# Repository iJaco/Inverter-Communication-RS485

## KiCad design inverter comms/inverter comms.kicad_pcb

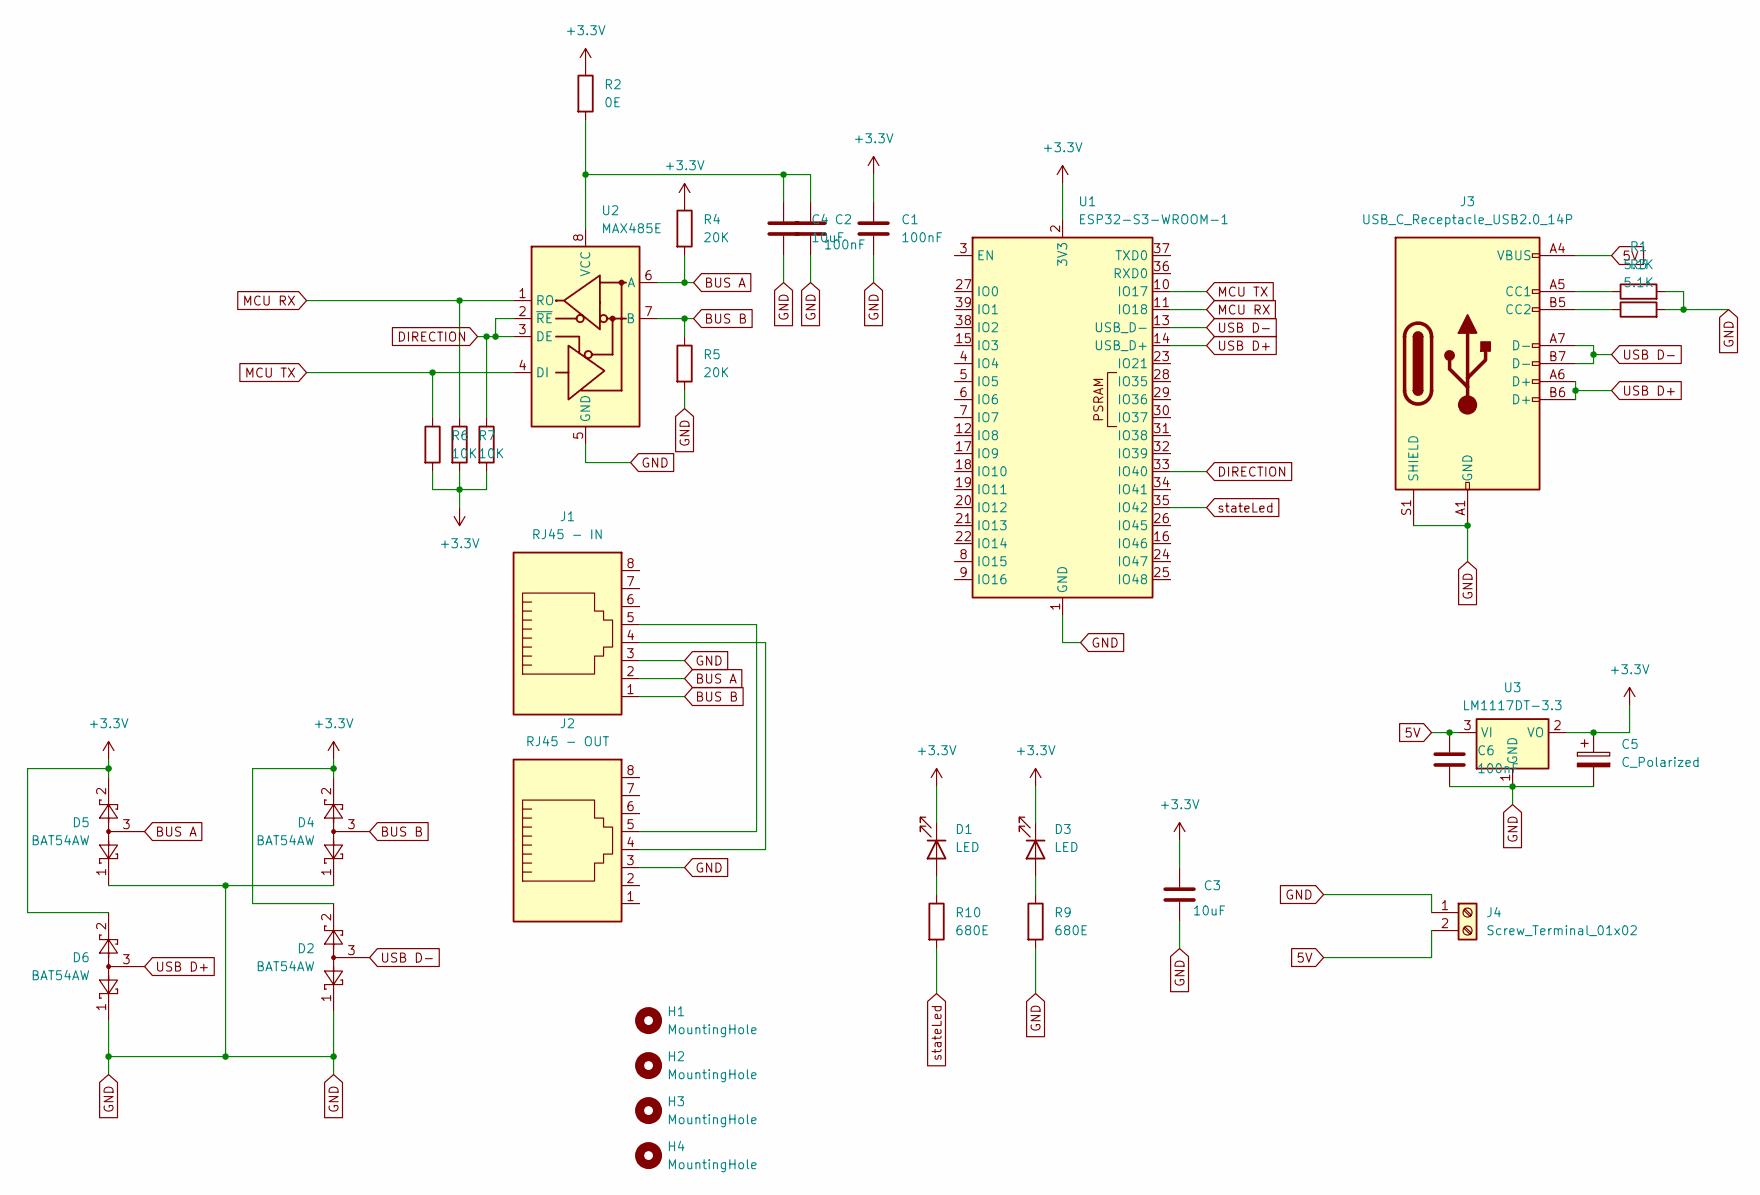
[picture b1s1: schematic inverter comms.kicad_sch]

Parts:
C1, C2, C6: 100nF; R_1206_3216Metric
C3, C4: 10uF; R_1206_3216Metric
C5: C_Polarized; C_1206_3216Metric_Pad1.33x1.80mm_HandSolder
D1, D3: LED; R_1206_3216Metric
D2, D4, D5, D6: BAT54AW; SOT-323_SC-70
H1, H2, H3, H4: MountingHole; MountingHole_3.2mm_M3
J1: RJ45 - IN; RJ45_OST_PJ012-8P8CX_Vertical
J2: RJ45 - OUT; RJ45_OST_PJ012-8P8CX_Vertical
J3: USB_C_Receptacle_USB2.0_14P; USB_C_Receptacle_GCT_USB4110
J4: Screw_Terminal_01x02; TerminalBlock_MaiXu_MX126-5.0-02P_1x02_P5.00mm
R1, R3: 5.1K; R_1206_3216Metric
R2: 0E; R_1206_3216Metric
R4, R5: 20K; R_1206_3216Metric
R6, R7, R8: 10K; R_1206_3216Metric
R9, R10: 680E; R_1206_3216Metric
U1: ESP32-S3-WROOM-1
U2: MAX485E; SOIC-8_3.9x4.9mm_P1.27mm
U3: LM1117DT-3.3; TO-252-3_TabPin2

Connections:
5V: C6.1, J3.A4 (VBUS), J3.A9 (VBUS), J3.B4 (VBUS), J3.B9 (VBUS), J4.2, U3.3 (VI)
+3.3V: C1.1, C3.1, C5.1, D1.1 (K), D2.2, D3.1 (K), D4.2, D5.2, D6.2, R2.1, R4.1, R6.2, R7.2, R8.2, U1.2 (3V3), U3.2 (VO)
BUS A: D5.3, J1.2, R4.2, U2.6 (A)
BUS B: D4.3, J1.1, R5.1, U2.7 (B)
DIRECTION: R8.1, U1.33 (IO40), U2.2 (~RE), U2.3 (DE)
GND: C1.2, C2.2, C3.2, C4.2, C5.2, C6.2, D2.1, D4.1, D5.1, D6.1, J1.3, J2.3, J3.A1 (GND), J3.A12 (GND), J3.B1 (GND), J3.B12 (GND), J3.S1 (SHIELD), J4.1, R1.2, R3.2, R5.2, R9.2, U1.1 (GND), U1.40 (GND), U1.41 (GND), U2.5 (GND), U3.1 (GND)
MCU RX: R7.1, U1.11 (IO18), U2.1 (RO)
MCU TX: R6.1, U1.10 (IO17), U2.4 (DI)
unnamed: D1.2 (A), R10.1
unnamed: D3.2 (A), R9.1
unnamed: J1.4, J2.4
unnamed: J1.5, J2.5
unnamed: J3.A5 (CC1), R1.1
unnamed: J3.B5 (CC2), R3.1
unnamed: C2.1, C4.1, R2.2, U2.8 (VCC)
USB D+: D6.3, J3.A6 (D+), J3.B6 (D+), U1.14 (USB_D+)
USB D-: D2.3, J3.A7 (D-), J3.B7 (D-), U1.13 (USB_D-)
stateLed: R10.2, U1.35 (IO42)

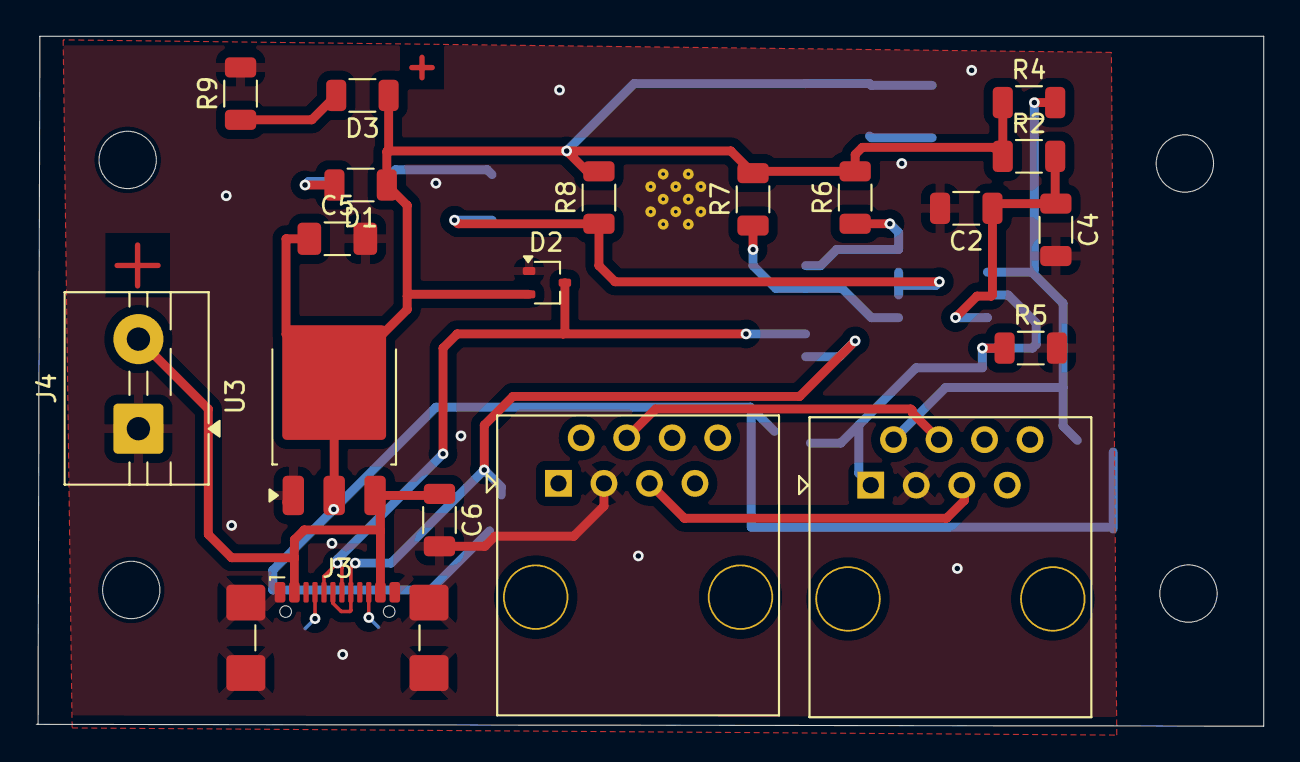
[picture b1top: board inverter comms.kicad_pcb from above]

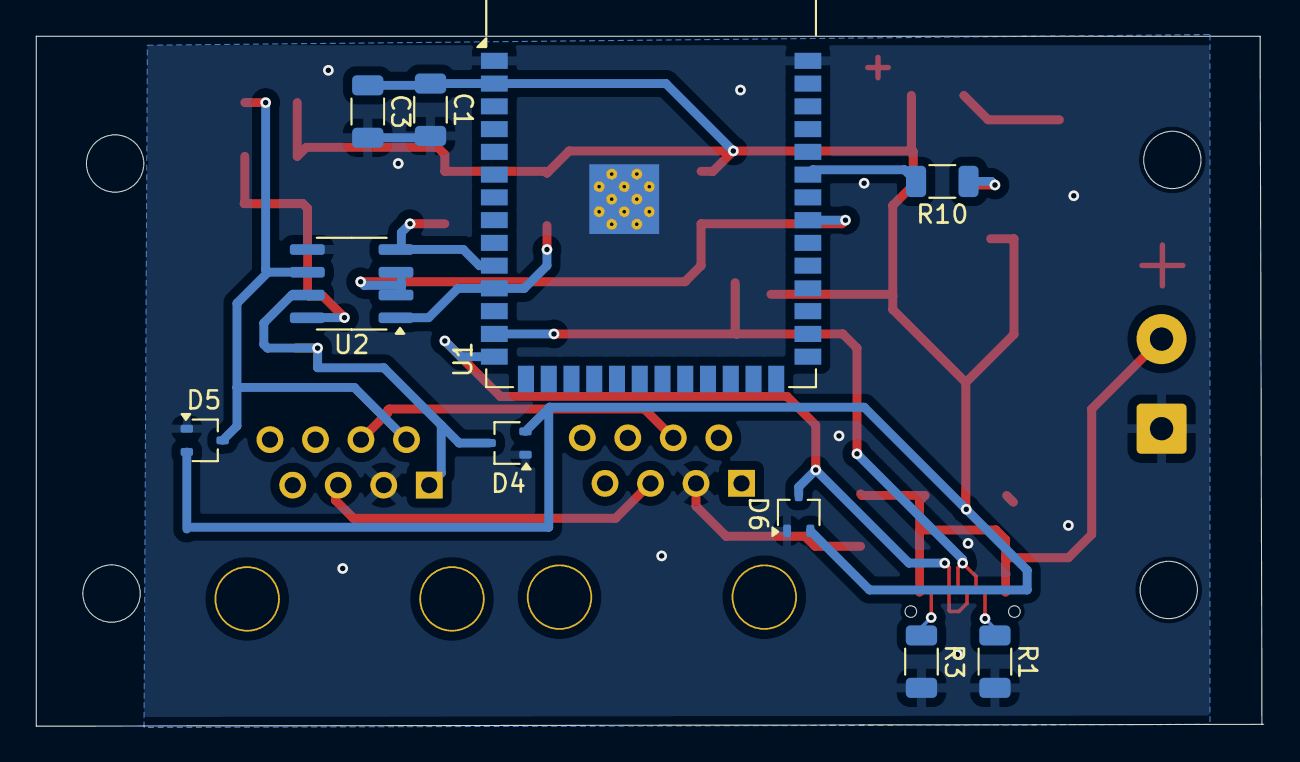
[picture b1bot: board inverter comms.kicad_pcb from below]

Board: 2 copper layers, 68.5 x 38.5 mm, 33 parts (10 on the bottom side), 18 nets.

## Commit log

2025-09-12 check in
2025-09-12 Cleanup
